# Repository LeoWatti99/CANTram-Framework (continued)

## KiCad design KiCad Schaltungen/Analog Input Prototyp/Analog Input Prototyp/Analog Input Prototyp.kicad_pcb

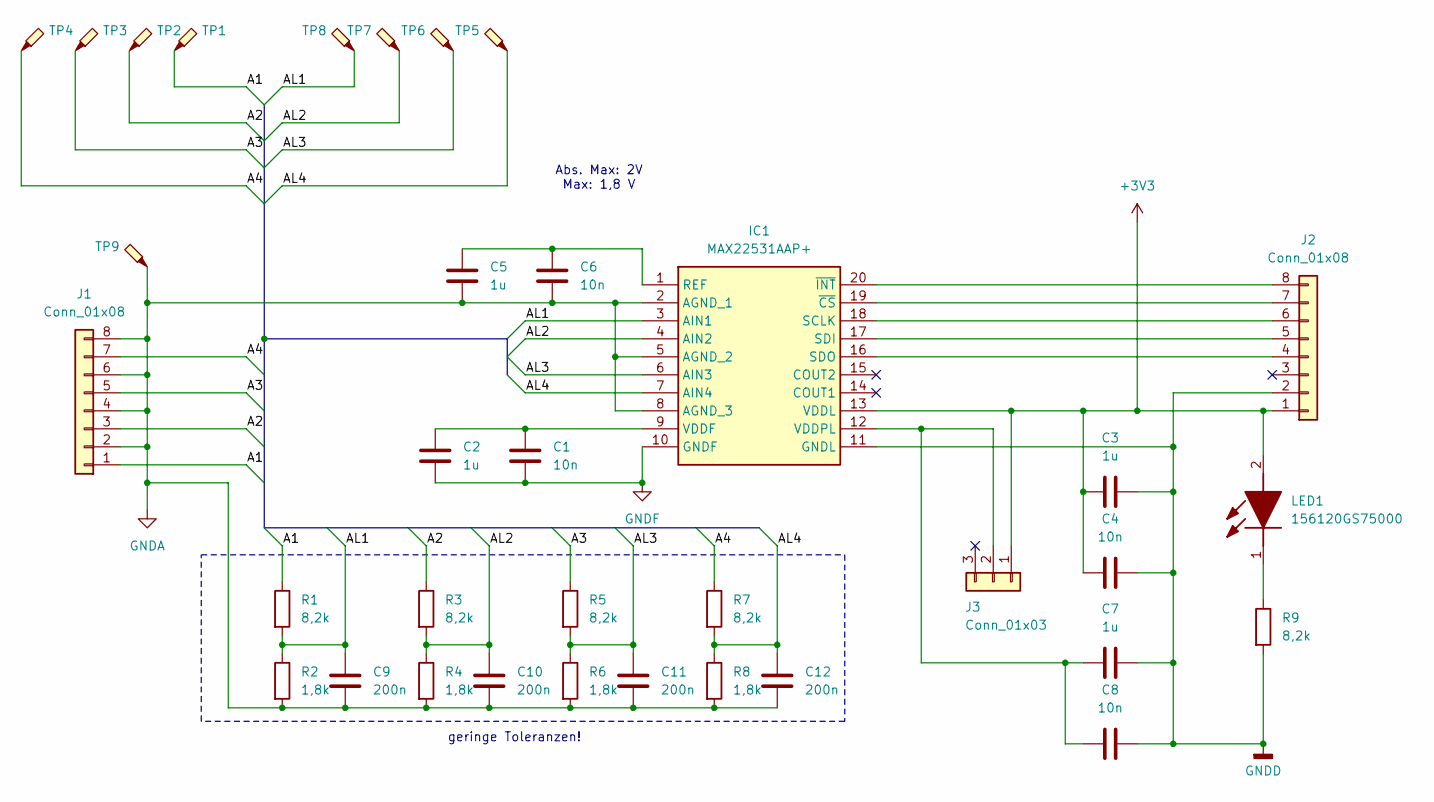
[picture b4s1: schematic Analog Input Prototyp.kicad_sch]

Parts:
C1, C4, C6, C8: 10n; C_1206_3216Metric; Manufacturer_Part_Number GRT3195C2A103JA02D; Mouser Part Number 81-GRT3195C2A103JA2D
C2, C3, C5, C7: 1u; C_1206_3216Metric; Manufacturer_Part_Number C1206X105J1RACTU; Mouser Part Number 80-C1206X105J1R
C9, C10, C11, C12: 200n; C_1206_3216Metric; Manufacturer_Part_Number C1206C224J1RECAUTO; Mouser Part Number 80-C1206C224J1RECAUT
IC1: MAX22531AAP+; SOP65P778X199-20N; Mouser Part Number 700-MAX22531AAP+
J1, J2: Conn_01x08; PinHeader_1x08_P2.54mm_Vertical
J3: Conn_01x03; PinHeader_1x03_P2.54mm_Vertical
LED1: 156120GS75000; Mouser Part Number 710-156120GS75000
R1, R3, R5, R7, R9: 8,2k; R_1206_3216Metric; Manufacturer_Part_Number CRGCQ1206F8K2; Mouser Part Number 279-CRGCQ1206F8K2
R2, R4, R6, R8: 1,8k; R_1206_3216Metric; Manufacturer_Part_Number CRCW12061K80FKEAC; Mouser Part Number 71-CRCW12061K80FKEAC
TP1, TP2, TP3, TP4, TP5, TP6, TP7, TP8, TP9: TestPoint_Probe; TestPoint_Keystone_5000-5004_Miniature; Manufacturer_Part_Number 5001; Mouser Part Number 534-5001

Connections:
+3V3: C3.1, C4.1, IC1.13 (VDDL), J2.1, J3.1, LED1.2 (A)
/A1: J1.1, R1.1, TP1.1
/A2: J1.3, R3.1, TP2.1
/A3: J1.5, R5.1, TP3.1
/A4: J1.7, R7.1, TP4.1
/AL1: C9.1, IC1.3 (AIN1), R1.2, R2.1, TP8.1
/AL2: C10.1, IC1.4 (AIN2), R3.2, R4.1, TP7.1
/AL3: C11.1, IC1.6 (AIN3), R5.2, R6.1, TP6.1
/AL4: C12.1, IC1.7 (AIN4), R7.2, R8.1, TP5.1
GNDA: C5.2, C6.2, C9.2, C10.2, C11.2, C12.2, IC1.2 (AGND_1), IC1.5 (AGND_2), IC1.8 (AGND_3), J1.2, J1.4, J1.6, J1.8, R2.2, R4.2, R6.2, R8.2, TP9.1
GNDD: C3.2, C4.2, C7.2, C8.2, IC1.11 (GNDL), J2.2, R9.2
GNDF: C1.2, C2.2, IC1.10 (GNDF)
unnamed: C5.1, C6.1, IC1.1 (REF)
unnamed: IC1.18 (SCLK), J2.6
unnamed: IC1.17 (SDI), J2.5
unnamed: IC1.16 (SDO), J2.4
unnamed: C1.1, C2.1, IC1.9 (VDDF)
unnamed: C7.1, C8.1, IC1.12 (VDDPL), J3.2
unnamed: IC1.19 (~CS), J2.7
unnamed: IC1.20 (~INT), J2.8
unnamed: LED1.1 (K), R9.1

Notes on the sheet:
geringe Toleranzen!
Abs. Max: 2V Max: 1,8 V

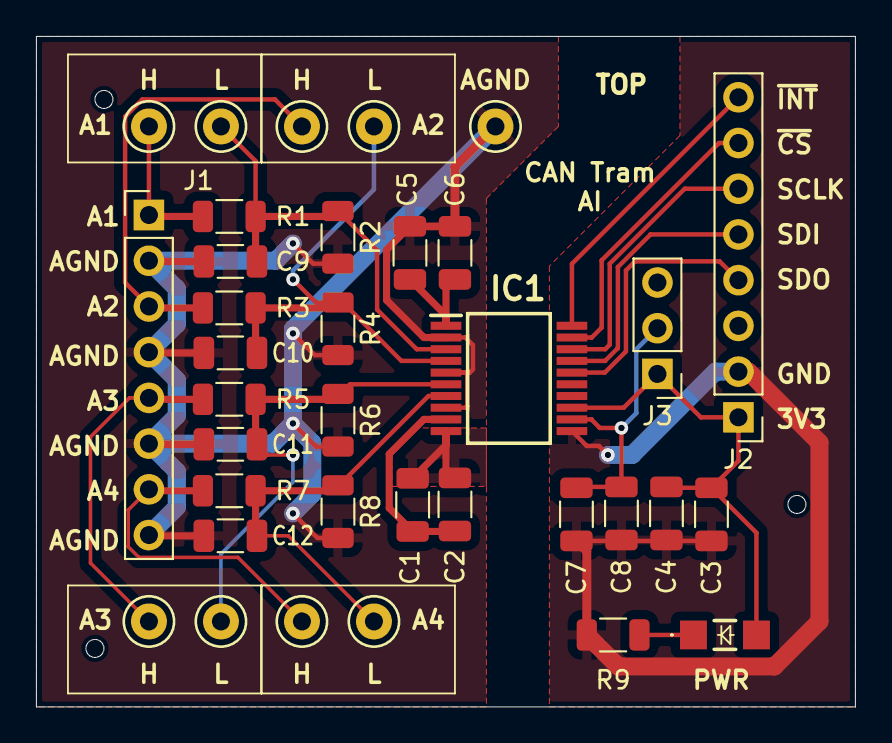
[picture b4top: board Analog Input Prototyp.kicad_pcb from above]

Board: 2 copper layers, 45.5 x 37.2 mm, 35 parts (0 on the bottom side), 21 nets.

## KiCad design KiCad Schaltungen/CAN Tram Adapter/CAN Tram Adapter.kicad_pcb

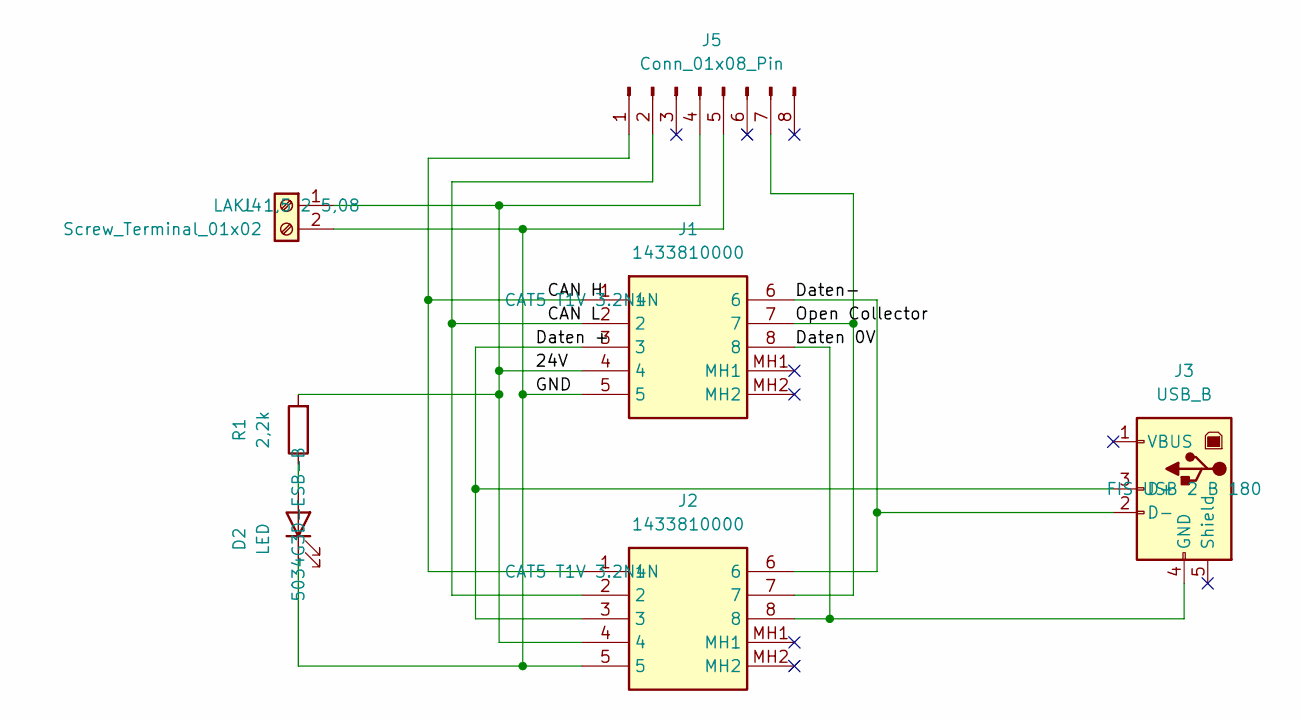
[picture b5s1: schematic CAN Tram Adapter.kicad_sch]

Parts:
D2: LED; LED_D5.0mm
J1, J2: 1433810000; Mouser Part Number 470-1433810000
J3: USB_B; Fischer_USB_2_B_180
J4: Screw_Terminal_01x02; TerminalBlock_Phoenix_MKDS-1,5-2-5.08_1x02_P5.08mm_Horizont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
J5: Conn_01x08_Pin; PinHeader_1x08_P2.54mm_Vertical
R1: 2,2k; R_Axial_DIN0207_L6.3mm_D2.5mm_P2.54mm_Vertical

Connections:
/24V: J1.4, J2.4, J4.1, J5.4, R1.2
/CAN H: J1.1, J2.1, J5.1
/CAN L: J1.2, J2.2, J5.2
/Daten 0V: J1.8, J2.8, J3.4 (GND)
/Daten +: J1.3, J2.3, J3.3 (D+)
/Daten-: J1.6, J2.6, J3.2 (D-)
/GND: D2.1 (K), J1.5, J2.5, J4.2, J5.5
/Open Collector: J1.7, J2.7, J5.7
unnamed: D2.2 (A), R1.1

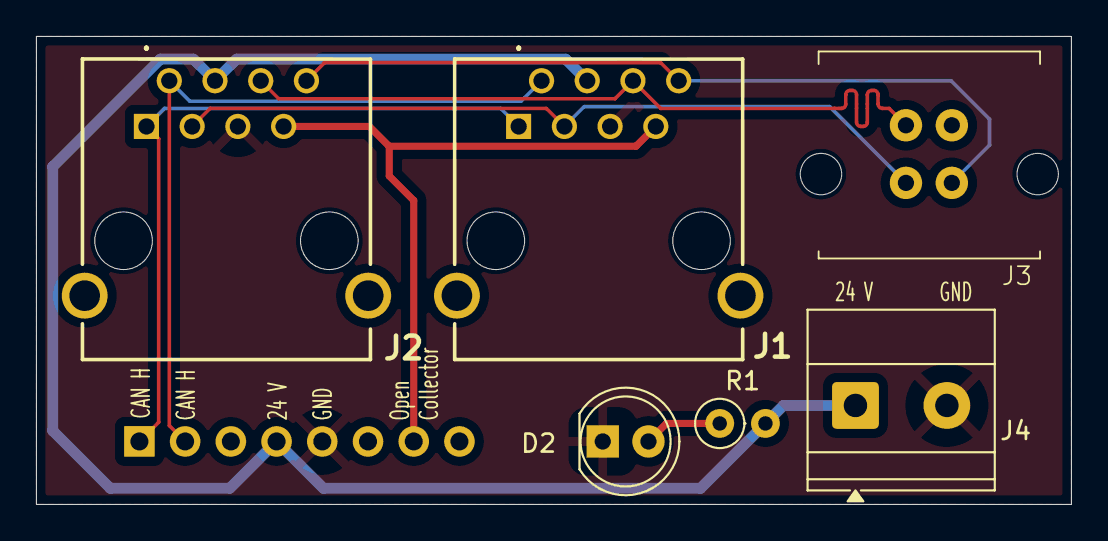
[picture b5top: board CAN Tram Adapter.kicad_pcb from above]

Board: 2 copper layers, 57.5 x 26.0 mm, 7 parts (1 on the bottom side), 9 nets.

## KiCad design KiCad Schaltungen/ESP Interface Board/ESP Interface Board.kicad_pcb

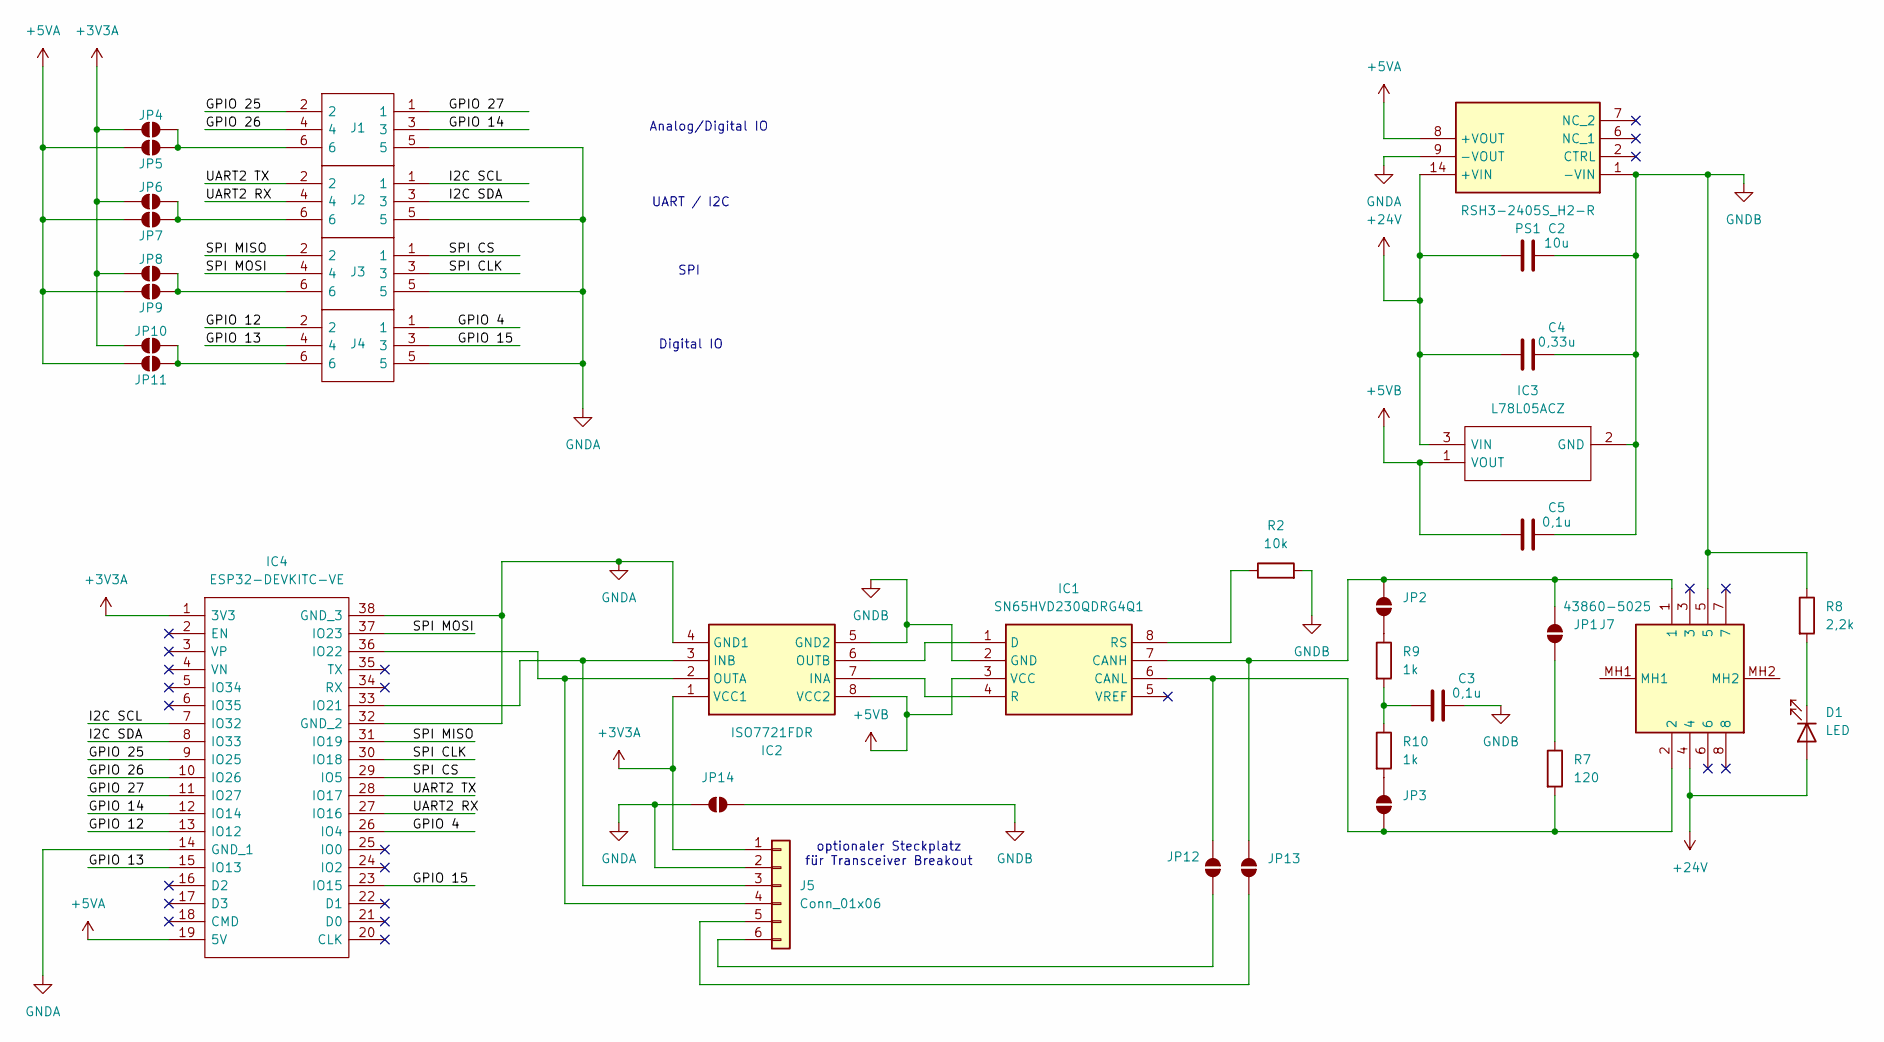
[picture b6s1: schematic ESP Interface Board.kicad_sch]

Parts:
C2: 10u; C_Disc_D5.1mm_W3.2mm_P5.00mm; Manufacturer_Part_Number CL31A106KBHNNNE; Mouser Part Number 187-CL31A106KBHNNNE
C3, C5: 0,1u; C_Disc_D5.1mm_W3.2mm_P5.00mm; Manufacturer_Part_Number CL31A106KBHNNNE; Mouser Part Number 187-CL31A106KBHNNNE
C4: 0,33u; C_Disc_D5.1mm_W3.2mm_P5.00mm; Manufacturer_Part_Number CL31A106KBHNNNE; Mouser Part Number 187-CL31A106KBHNNNE
D1: LED; LED_D5.0mm
IC1: SN65HVD230QDRG4Q1; SOIC127P600X175-8N; Mouser Part Number 595-S65HVD230QDRG4Q1
IC2: ISO7721FDR; SOIC127P600X175-8N; Mouser Part Number 595-ISO7721FDR
IC3: L78L05ACZ; Mouser Part Number 511-L78L05ACZ
IC4: ESP32-DEVKITC-VE; ESP32DEVKITCVE; Manufacturer_Part_Number ESP32-DEVKITC-VE; Mouser Part Number 356-ESP32-DEVKTC32VE
J1, J2, J3, J4: DG127A-5.08-06P-14-00AH; DG127A50806P1400AH; Manufacturer_Part_Number DG127A-5.08-06P-14-00AH
J5: Conn_01x06; PinSocket_1x06_P2.54mm_Vertical
J7: 43860-5025; 438605025; Mouser Part Number 538-43860-5025
JP1, JP2, JP3, JP4, JP5, JP6, JP7, JP8, JP9, JP10, JP11, JP12, JP13, JP14: SolderJumper_2_Open; SolderJumper-2_P1.3mm_Open_Pad1.0x1.5mm
PS1: RSH3-2405S_H2-R; RSH32405SH2R; Mouser Part Number 919-RSH3-2405S/H2-R
R2: 10k; R_Axial_DIN0207_L6.3mm_D2.5mm_P7.62mm_Horizontal; Manufacturer_Part_Number RC1206FR-1310KL; Mouser Part Number 603-RC1206FR-1310KL
R7: 120; R_Axial_DIN0207_L6.3mm_D2.5mm_P7.62mm_Horizontal
R8: 2,2k; R_Axial_DIN0207_L6.3mm_D2.5mm_P7.62mm_Horizontal
R9, R10: 1k; R_Axial_DIN0207_L6.3mm_D2.5mm_P7.62mm_Horizontal

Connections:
+3V3A: IC2.1 (VCC1), IC4.1 (3V3), J5.1, JP4.2 (B), JP6.2 (B), JP8.2 (B), JP10.2 (B)
+5VA: IC4.19 (5V), JP5.2 (B), JP7.2 (B), JP9.2 (B), JP11.2 (B), PS1.8 (+VOUT)
+5VB: C5.1, IC1.3 (VCC), IC2.8 (VCC2), IC3.1 (VOUT)
+24V: C2.1, C4.1, D1.2 (A), IC3.3 (VIN), J7.4, PS1.14 (+VIN)
/GPIO 4: IC4.26 (IO4), J4.1
/GPIO 12: IC4.13 (IO12), J4.2
/GPIO 13: IC4.15 (IO13), J4.4
/GPIO 14: IC4.12 (IO14), J1.3
/GPIO 15: IC4.23 (IO15), J4.3
/GPIO 25: IC4.9 (IO25), J1.2
/GPIO 26: IC4.10 (IO26), J1.4
/GPIO 27: IC4.11 (IO27), J1.1
/I2C SCL: IC4.7 (IO32), J2.1
/I2C SDA: IC4.8 (IO33), J2.3
/SPI CLK: IC4.30 (IO18), J3.3
/SPI CS: IC4.29 (IO5), J3.1
/SPI MISO: IC4.31 (IO19), J3.2
/SPI MOSI: IC4.37 (IO23), J3.4
/UART2 RX: IC4.27 (IO16), J2.4
/UART2 TX: IC4.28 (IO17), J2.2
GNDA: IC2.4 (GND1), IC4.14 (GND_1), IC4.32 (GND_2), IC4.38 (GND_3), J1.5, J2.5, J3.5, J4.5, J5.2, JP14.2 (B), PS1.9 (-VOUT)
GNDB: C2.2, C3.2, C4.2, C5.2, IC1.2 (GND), IC2.5 (GND2), IC3.2 (GND), J7.5, JP14.1 (A), PS1.1 (-VIN), R2.2, R8.1
unnamed: C3.1, R9.2, R10.1
unnamed: D1.1 (K), R8.2
unnamed: IC1.7 (CANH), J7.1, JP1.2 (B), JP2.2 (B), JP13.2 (B)
unnamed: IC1.6 (CANL), J7.2, JP3.1 (A), JP12.2 (B), R7.2
unnamed: IC1.1 (D), IC2.6 (OUTB)
unnamed: IC1.4 (R), IC2.7 (INA)
unnamed: IC1.8 (RS), R2.1
unnamed: IC2.3 (INB), IC4.33 (IO21), J5.3
unnamed: IC2.2 (OUTA), IC4.36 (IO22), J5.4
unnamed: J5.5, JP13.1 (A)
unnamed: J5.6, JP12.1 (A)
unnamed: JP1.1 (A), R7.1
unnamed: JP2.1 (A), R9.1
unnamed: JP3.2 (B), R10.2
unnamed: J1.6, JP4.1 (A), JP5.1 (A)
unnamed: J2.6, JP6.1 (A), JP7.1 (A)
unnamed: J3.6, JP8.1 (A), JP9.1 (A)
unnamed: J4.6, JP10.1 (A), JP11.1 (A)

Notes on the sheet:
optionaler Steckplatz für Transceiver Breakout
Digital IO
UART / I2C
SPI
Analog/Digital IO

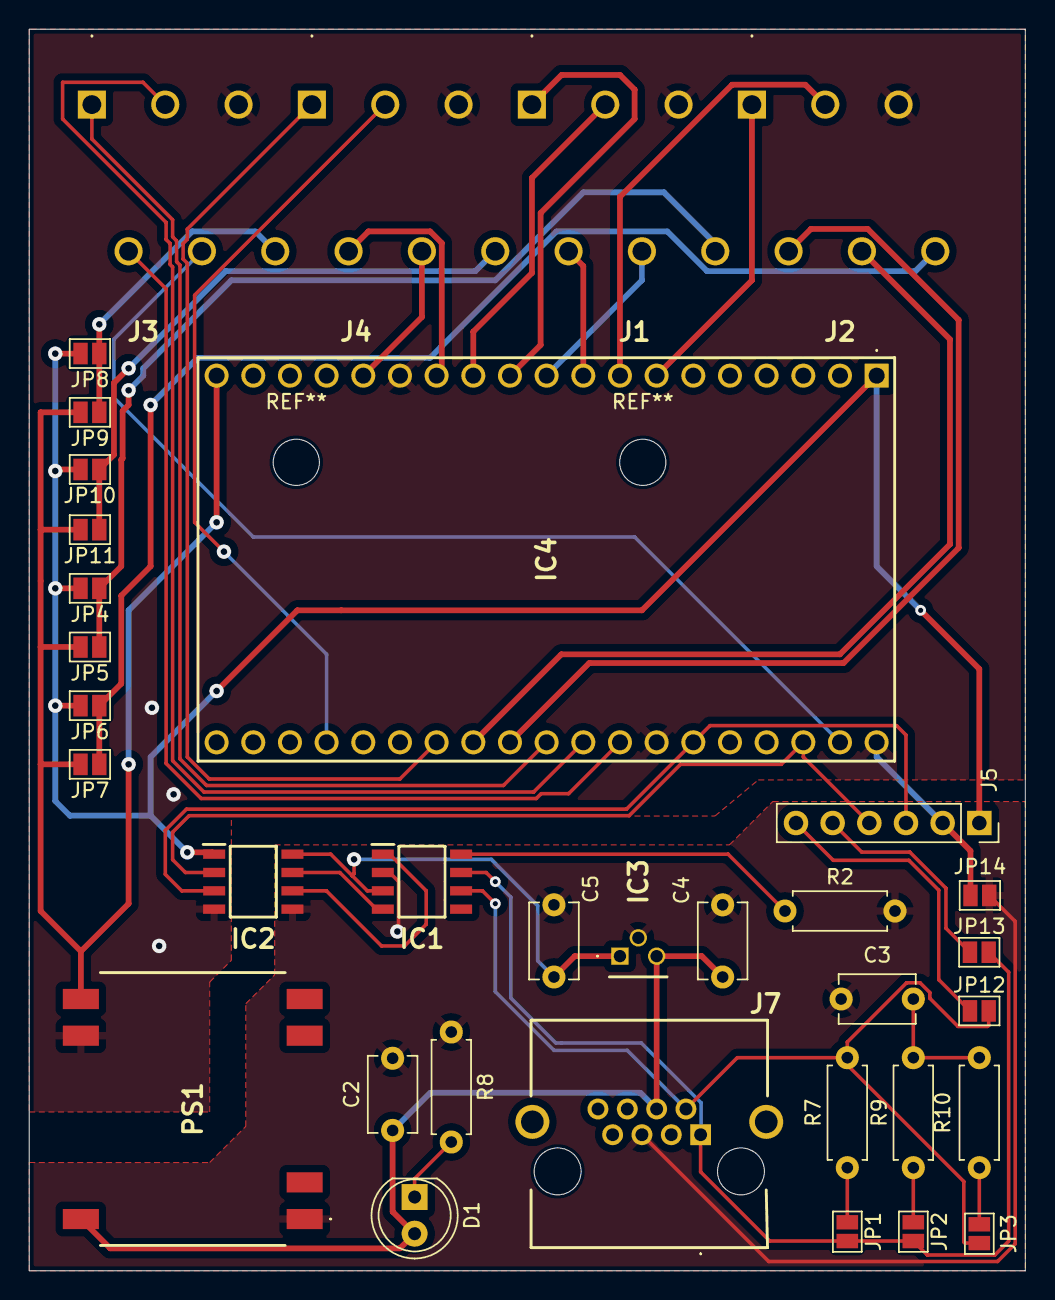
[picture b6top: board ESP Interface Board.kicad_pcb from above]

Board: 2 copper layers, 69.0 x 86.0 mm, 35 parts (0 on the bottom side), 40 nets.

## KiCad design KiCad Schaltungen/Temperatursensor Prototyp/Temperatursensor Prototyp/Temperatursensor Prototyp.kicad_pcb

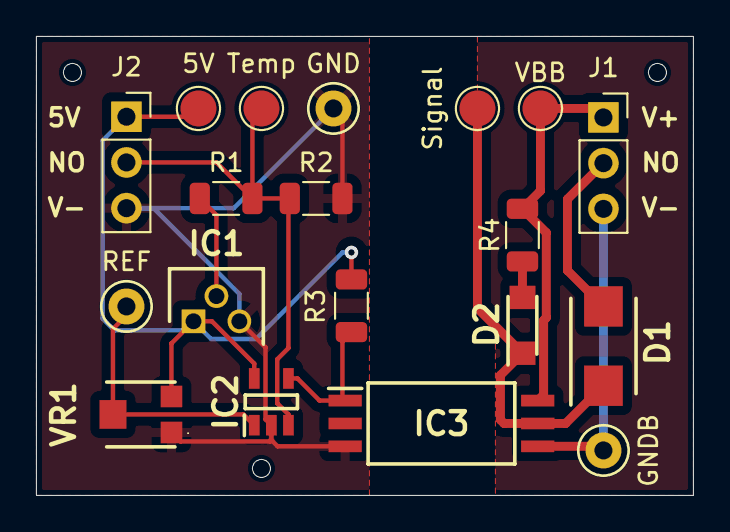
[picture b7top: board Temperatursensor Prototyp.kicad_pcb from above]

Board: 2 copper layers, 36.5 x 25.5 mm, 19 parts (0 on the bottom side), 11 nets.

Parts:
5V: TestPoint; TestPoint_Pad_D2.0mm
D1: D; DIOM5336X250N
D2: Rot; LEDM3216X130N
GND: TestPoint_Probe; TestPoint_Keystone_5000-5004_Miniature
GNDB: TestPoint_Probe; TestPoint_Keystone_5000-5004_Miniature
IC1: AD22100KTZ; TO128P419X483X533-3P
IC2: LMV331ILT; SOT95P280X145-5N
IC3: VOFD341A-X008T; SOIC127P1150X378-6N
J1, J2: Conn_01x03; PinSocket_1x03_P2.54mm_Vertical
R1, R4: 6,2k; R_1206_3216Metric
R2: 12k; R_1206_3216Metric
R3: 220; R_1206_3216Metric
REF: TestPoint_Probe; TestPoint_Keystone_5000-5004_Miniature
Signal: TestPoint; TestPoint_Pad_D2.0mm
Temp: TestPoint; TestPoint_Pad_D2.0mm
VBB: TestPoint; TestPoint_Pad_D2.0mm
VR1: TC33X-2-503E; TC33X2503E

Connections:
+5V: 5V.1, IC1.1 (V+), IC2.5 (VCC+), J2.1, R3.2, VR1.3 (CW)
/V_Temp: IC2.3 (IN-), J2.2, R1.2, R2.1, Temp.1
GND: GND.1, IC1.3 (GND), IC2.2 (VCC-), IC3.3 (C), J2.3, R2.2, VR1.1 (CCW)
GNDBB: GNDB.1, IC3.4 (VEE), J1.3
unnamed: D1.2 (A), J1.2
unnamed: D1.1 (K), D2.1 (K), IC3.5 (VO), Signal.1
unnamed: IC1.2 (VO), R1.1
unnamed: IC2.1 (IN+), REF.1, VR1.2 (WIPER)
unnamed: IC2.4 (OUT), IC3.1 (A), R3.1
unnamed: IC3.6 (VCC), J1.1, R4.2, VBB.1
unnamed: D2.2 (A), R4.1

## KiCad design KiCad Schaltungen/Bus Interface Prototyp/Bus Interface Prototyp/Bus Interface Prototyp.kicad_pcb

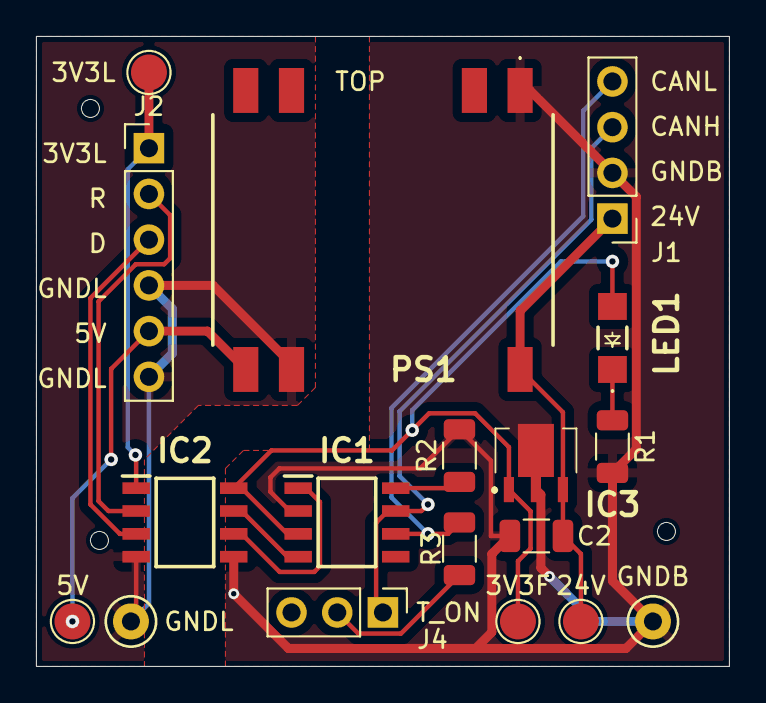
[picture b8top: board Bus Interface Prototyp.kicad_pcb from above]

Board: 2 copper layers, 38.5 x 35.0 mm, 18 parts (0 on the bottom side), 15 nets.

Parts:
3V3F, 3V3L, 5V, 24V: TestPoint; TestPoint_Pad_D2.0mm
C2: 10u; C_1206_3216Metric
GNDB: TestPoint_Probe; TestPoint_Keystone_5000-5004_Miniature
GNDL: TestPoint_Probe; TestPoint_Keystone_5000-5004_Miniature
IC1: SN65HVD230QDRG4Q1; SOIC127P600X175-8N
IC2: ISO7721FDR; SOIC127P600X175-8N
IC3: L78L33ABUTR
J1: Conn_01x04; PinHeader_1x04_P2.54mm_Vertical
J2: Conn_01x06; PinHeader_1x06_P2.54mm_Vertical
J4: Conn_01x03; PinHeader_1x03_P2.54mm_Vertical
LED1: 156120GS75000
PS1: RSH3-2405S_H2-R; RSH32405SH2R
R1: 470; R_1206_3216Metric
R2: 10k; R_1206_3216Metric
R3: 120; R_1206_3216Metric

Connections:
+3V3B: 3V3F.1, IC1.3 (VCC), IC2.8 (VCC2), IC3.1 (VOUT), LED1.2 (A)
+5V: 5V.1, J2.5, PS1.8 (+VOUT)
+24V: 24V.1, C2.1, IC3.3 (VIN), J1.1, PS1.14 (+VIN)
GNDB: C2.2, GNDB.1, IC1.2 (GND), IC2.5 (GND2), IC3.2 (GND_1), IC3.4 (GND_2), J1.2, PS1.1 (-VIN), R1.2, R2.2
GNDL: GNDL.1, IC2.4 (GND1), J2.4, J2.6, PS1.9 (-VOUT)
unnamed: IC1.7 (CANH), J1.3, J4.1
unnamed: IC1.6 (CANL), J1.4, R3.2
unnamed: IC1.1 (D), IC2.6 (OUTB)
unnamed: IC1.4 (R), IC2.7 (INA)
unnamed: IC1.8 (RS), R2.1
unnamed: IC2.3 (INB), J2.3
unnamed: IC2.2 (OUTA), J2.2
unnamed: 3V3L.1, IC2.1 (VCC1), J2.1
unnamed: J4.2, R3.1
unnamed: LED1.1 (K), R1.1

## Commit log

2025-12-14 Initial plan
2025-12-14 Add comprehensive C++ framework structure with libraries and documentation
2025-12-14 Add quick start guide, changelog, and improve documentation
2025-12-14 Add complete implementations for DigitalIO and Timer libraries
2025-12-14 Address code review feedback: improve implementations and add clarifying comments
2025-12-14 Enhance README with CANTram framework details
    Added a description of the CANTram framework and its components.
2025-12-14 Complete CANTram Framework structure - ready for library expansion
2025-12-14 Fix CANCore stub implementation to avoid misleading success indicators
2025-12-14 Added basic library structure
2025-12-14 Added all source code files
2026-01-13 added doxygen documentation
2026-01-13 Added documentation
2026-01-14 Test
2026-01-14 Add GitHub Actions workflow for Doxygen documentation
2026-01-14 Added automation
2026-01-14 Add workflow_dispatch to main.yml
    Enable manual triggering of the workflow.
2026-01-14 deploy: 415b3fa45ff671a96b6898241338defac82f736c
2026-01-14 Change publish directory for Doxygen documentation
2026-01-14 Changed documentation in RelaisModuleV1_0
2026-01-14 Update GitHub Actions workflow for main branch
2026-01-14 deploy: 0b33e37096fc1958178a46329c9c4a4ec64b6952
2026-01-24 reordered framework directories
2026-01-24 fixed doxygen action
2026-01-24 deploy: 9a6de6e7ccfc667ae31968b17fce9a567c292de6
2026-01-24 Added KiCad circuit files and inventor CAD files
2026-01-24 Revise README with new project details and image
    Updated project description and added image reference.
2026-01-24 Update README with documentation information
    Added documentation section with Doxygen link.
2026-01-24 removed esp32 cad modell cause its name caused probelms
